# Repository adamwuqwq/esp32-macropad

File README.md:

# macropad

## Introduction
A low-budget macro numeric keypad based on ESP32 MCU and CH9329 USB HID emulation chip.  

## Functions
### Keys and Layout
1. Standard 10-key layout + 5 function keys
2. All key macro support
3. Up to 5 macro profiles (stored in MCU's internal storage)

### Connectivity
1. USB 2.0 HID (CH9329 based) 
2. Built-in USB hub, 1 external USB port, 1 internal USB (based on FE1.1s)
3. USB UART debugging (based on CH340C)
4. Bluetooth 4.2 BLE HID   
5. 2.4GHz Wi-Fi (for configuration and OTA firmware update)

### Power Supply & Power Management
1. 3.7V Li-ion battery charging and management (based on TP5400)
2. Supports MCU's deep sleep and hibernation. 

### UI & User Interaction
1. 0.91' built-in I2C OLED screen
2. Cross-platform configuration App on PC using Qt/PyQt
3. Web configuration interface

### Others
1. USB HID Mouse emulation
2. TBD

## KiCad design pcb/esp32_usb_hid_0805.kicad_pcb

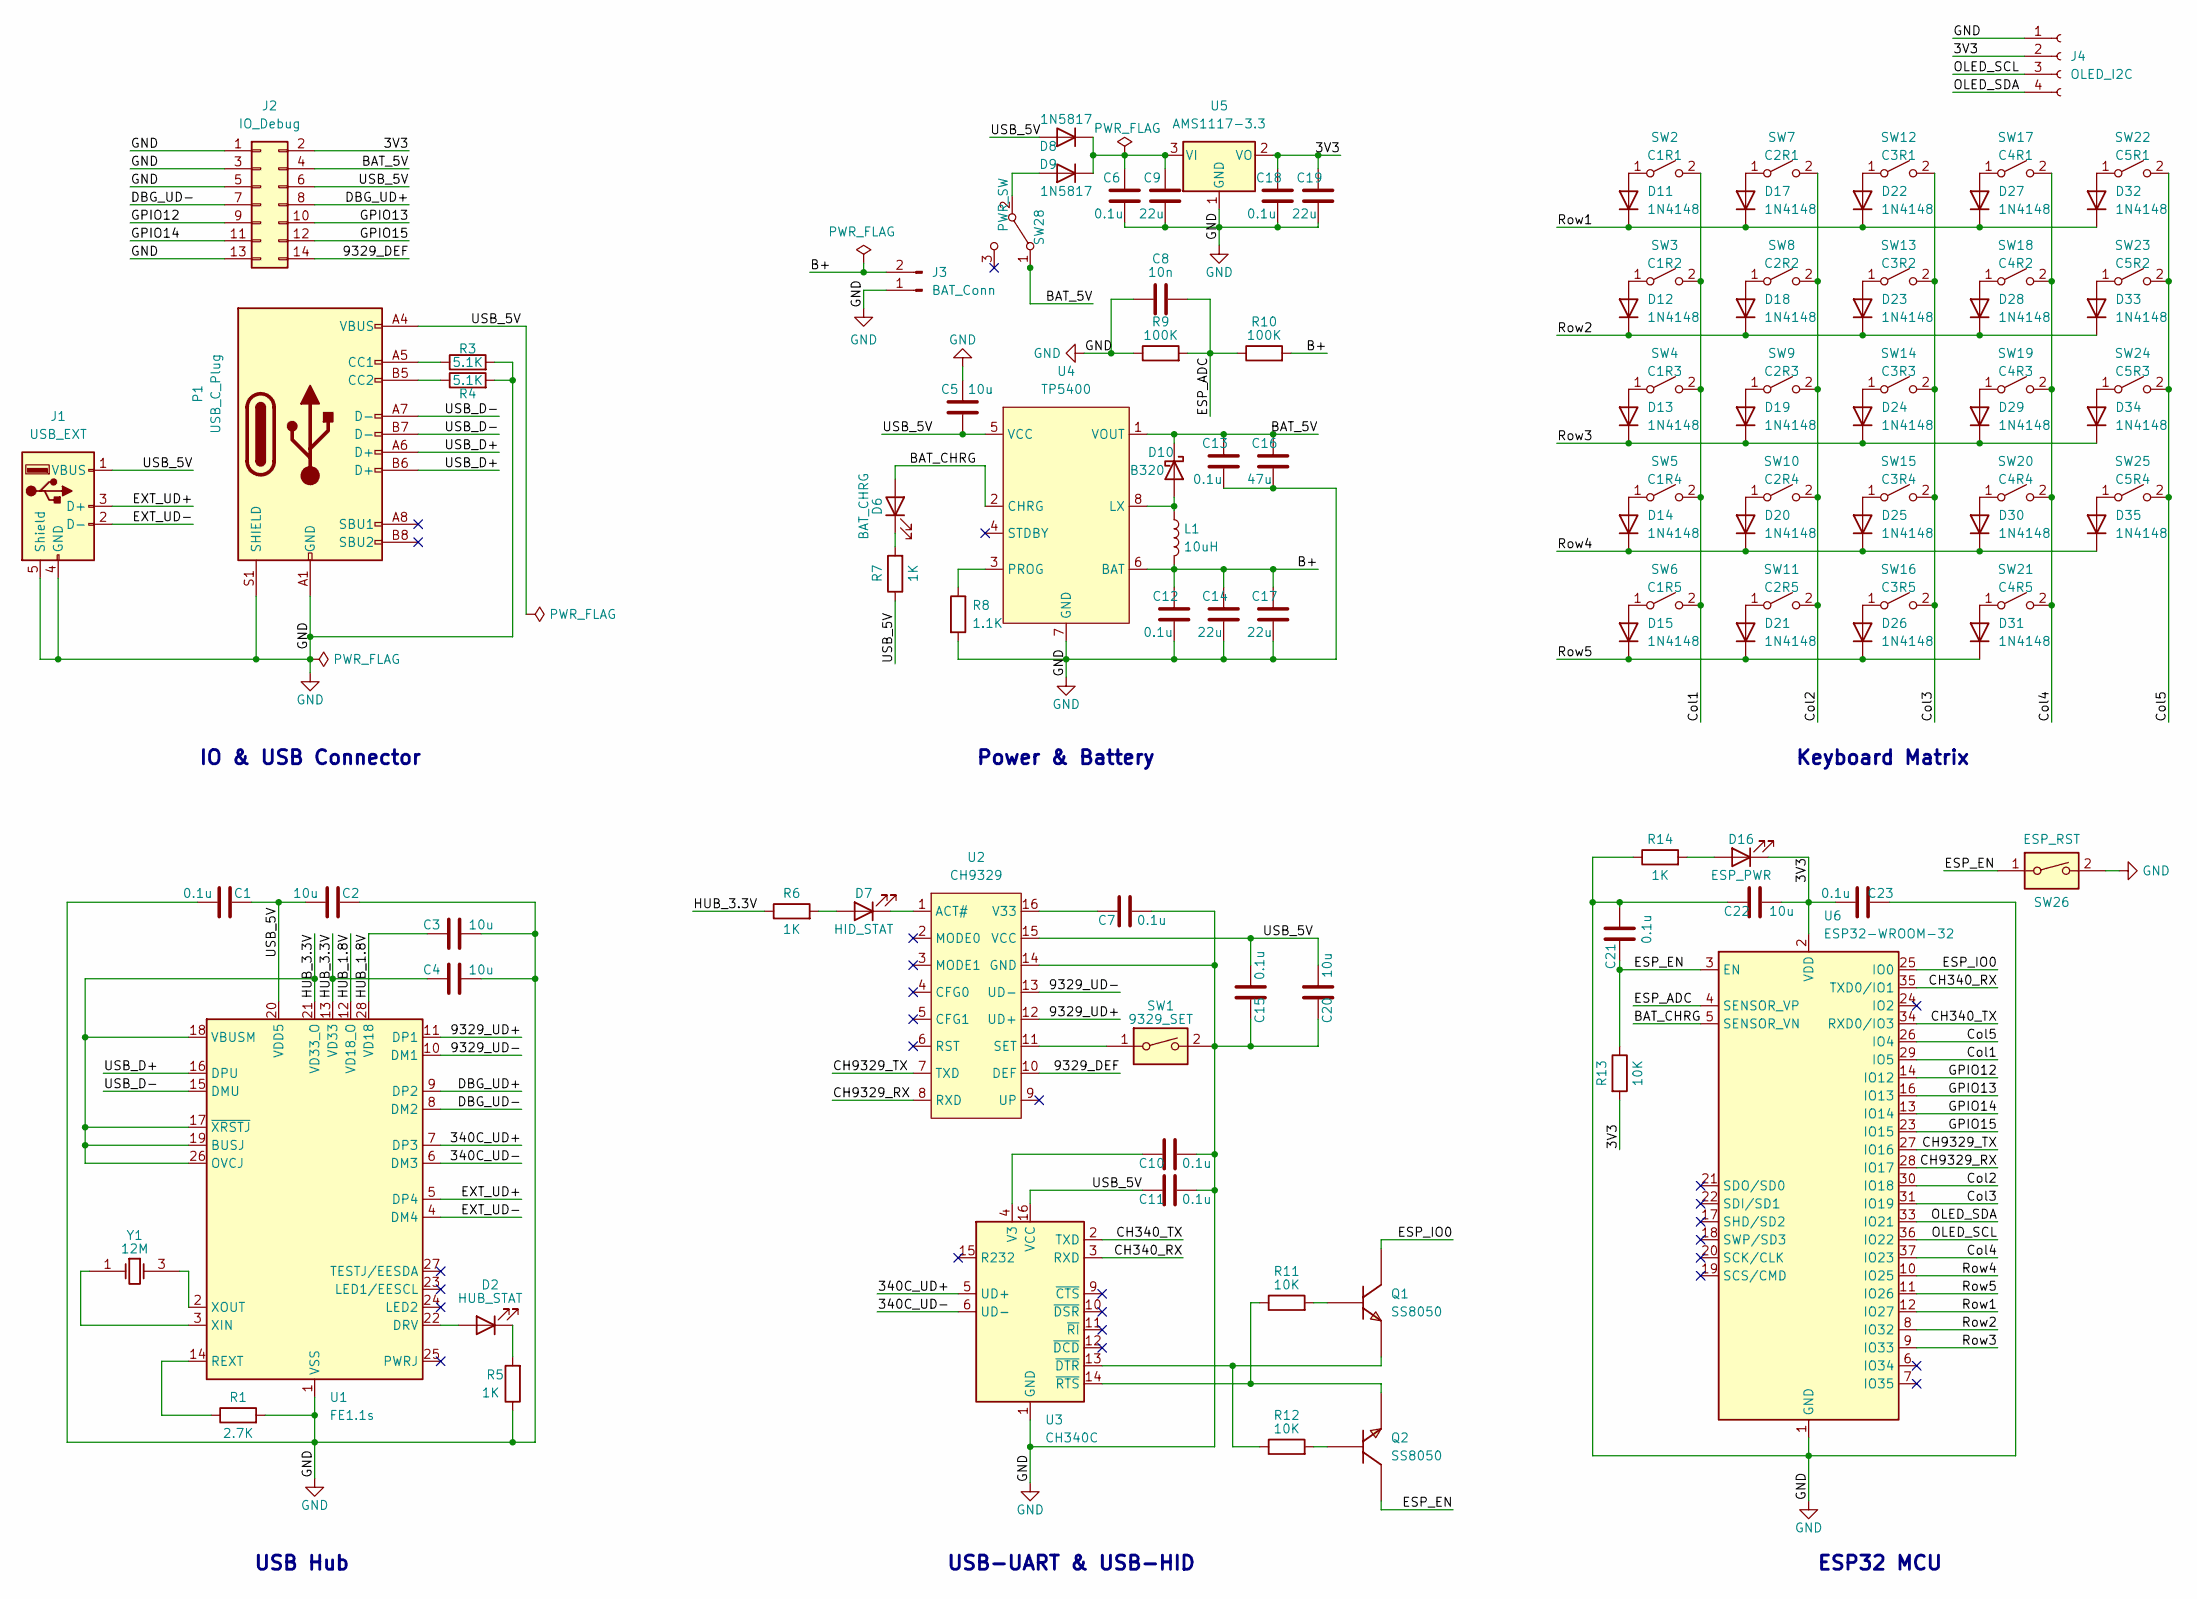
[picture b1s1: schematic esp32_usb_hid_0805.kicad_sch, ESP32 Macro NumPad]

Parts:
C1, C6, C7, C10, C11, C12, C13, C15, C18, C21, C23: 0.1u; C_0805_2012Metric
C2, C3, C4, C5, C20, C22: 10u; C_0805_2012Metric
C8: 10n; C_0805_2012Metric
C9, C14, C17, C19: 22u; C_0805_2012Metric
C16: 47u; C_0805_2012Metric
D2: HUB_STAT; LED_0805_2012Metric
D6: BAT_CHRG; LED_0805_2012Metric
D7: HID_STAT; LED_0805_2012Metric
D8, D9: 1N5817; D_SOD-123
D10: B320; D_SMA
D11, D12, D13, D14, D15, D17, D18, D19, D20, D21, D22, D23, D24, D25, D26, D27, D28, D29, D30, D31, D32, D33, D34, D35: 1N4148; D_SOD-123
D16: ESP_PWR; LED_0805_2012Metric
J1: USB_EXT; USB_A_Stewart_SS-52100-001_Horizontal
J2: IO_Debug; PinHeader_2x08_P2.54mm_Vertical
J3: BAT_Conn; PinHeader_2x01_P2.00mm_Vertical_SMD
J4: OLED_I2C; PinSocket_1x04_P2.54mm_Vertical
L1: 10uH; L_Coilcraft_XxL4020
P1: USB_C_Plug; USB_C_Receptacle_GCT_USB4085
Q1, Q2: SOT-23_SS8050_Y1; SOT-23
R1: 2.7K; R_0805_2012Metric
R3, R4: 5.1K; R_0805_2012Metric
R5, R6, R7, R14: 1K; R_0805_2012Metric
R8: 1.1K; R_0805_2012Metric
R9, R10: 100K; R_0805_2012Metric
R11, R12, R13: 10K; R_0805_2012Metric
SW1: 9329_SET; SW_SPST_CK_RS282G05A3
SW2: C1R1; SW_Cherry_MX_1.00u_PCB
SW3: C1R2; SW_Cherry_MX_1.00u_PCB
SW4: C1R3; SW_Cherry_MX_1.00u_PCB
SW5: C1R4; SW_Cherry_MX_1.00u_PCB
SW6: C1R5; SW_Cherry_MX_1.00u_PCB
SW7: C2R1; SW_Cherry_MX_1.00u_PCB
SW8: C2R2; SW_Cherry_MX_1.00u_PCB
SW9: C2R3; SW_Cherry_MX_1.00u_PCB
SW10: C2R4; SW_Cherry_MX_1.00u_PCB
SW11: C2R5; SW_Cherry_MX_1.00u_PCB
SW12: C3R1; SW_Cherry_MX_1.00u_PCB
SW13: C3R2; SW_Cherry_MX_1.00u_PCB
SW14: C3R3; SW_Cherry_MX_1.00u_PCB
SW15: C3R4; SW_Cherry_MX_1.00u_PCB
SW16: C3R5; SW_Cherry_MX_1.00u_PCB
SW17: C4R1; SW_Cherry_MX_1.00u_PCB
SW18: C4R2; SW_Cherry_MX_1.00u_PCB
SW19: C4R3; SW_Cherry_MX_1.00u_PCB
SW20: C4R4; SW_Cherry_MX_1.00u_PCB
SW21: C4R5; SW_Cherry_MX_1.00u_PCB
SW22: C5R1; SW_Cherry_MX_1.00u_PCB
SW23: C5R2; SW_Cherry_MX_1.00u_PCB
SW24: C5R3; SW_Cherry_MX_1.00u_PCB
SW25: C5R4; SW_Cherry_MX_2.00u_Vertical_PCB
SW26: ESP_RST; SW_SPST_CK_RS282G05A3
SW28: PWR_SW; SW_SPDT_PCM12
U1: FE1.1s; SSOP-28_3.9x9.9mm_P0.635mm
U2: CH9329; SOP-16_3.9x9.9mm_P1.27mm
U3: CH340C; SOIC-16_3.9x9.9mm_P1.27mm
U4: TP5400; HTSOP-8-1EP_3.9x4.9mm_P1.27mm_EP2.4x3.2mm
U5: AMS1117-3.3; SOT-223-3_TabPin2
U6: ESP32-WROOM-32
Y1: SMD-3225_4P__12MHZ_20PF_10PPM; Crystal_SMD_TXC_7M-4Pin_3.2x2.5mm

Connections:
/3V3: C18.1, C19.1, C22.2, C23.2, D16.1 (K), J2.2, J4.2, R13.2, U5.2 (VO), U6.2 (VDD)
/340C_UD+: U1.7 (DP3), U3.5 (UD+)
/340C_UD-: U1.6 (DM3), U3.6 (UD-)
/9329_DEF: J2.14, U2.10 (DEF)
/9329_UD+: U1.11 (DP1), U2.12 (UD+)
/9329_UD-: U1.10 (DM1), U2.13 (UD-)
/B+: C12.1, C14.1, C17.1, J3.2, L1.2, R10.2, U4.6 (BAT)
/BAT_5V: C13.1, C16.1, D10.1 (K), J2.4, SW28.1 (A), U4.1 (VOUT)
/BAT_CHRG: D6.2 (A), U4.2 (CHRG), U6.5 (SENSOR_VN)
/CH340_RX: U3.3 (RXD), U6.35 (TXD0/IO1)
/CH340_TX: U3.2 (TXD), U6.34 (RXD0/IO3)
/CH9329_RX: U2.8 (RXD), U6.28 (IO17)
/CH9329_TX: U2.7 (TXD), U6.27 (IO16)
/Col1: SW2.2 (B), SW3.2 (B), SW4.2 (B), SW5.2 (B), SW6.2 (B), U6.29 (IO5)
/Col2: SW7.2 (B), SW8.2 (B), SW9.2 (B), SW10.2 (B), SW11.2 (B), U6.30 (IO18)
/Col3: SW12.2 (B), SW13.2 (B), SW14.2 (B), SW15.2 (B), SW16.2 (B), U6.31 (IO19)
/Col4: SW17.2 (B), SW18.2 (B), SW19.2 (B), SW20.2 (B), SW21.2 (B), U6.37 (IO23)
/Col5: SW22.2 (B), SW23.2 (B), SW24.2 (B), SW25.2 (B), U6.26 (IO4)
/DBG_UD+: J2.8, U1.9 (DP2)
/DBG_UD-: J2.7, U1.8 (DM2)
/ESP_ADC: C8.2, R9.2, R10.1, U6.4 (SENSOR_VP)
/ESP_EN: C21.1, Q2.3 (C), R13.1, SW26.1, U6.3 (EN)
/ESP_IO0: Q1.3 (C), U6.25 (IO0)
/EXT_UD+: J1.3 (D+), U1.5 (DP4)
/EXT_UD-: J1.2 (D-), U1.4 (DM4)
/GPIO12: J2.9, U6.14 (IO12)
/GPIO13: J2.10, U6.16 (IO13)
/GPIO14: J2.11, U6.13 (IO14)
/GPIO15: J2.12, U6.23 (IO15)
/HUB_1.8V: C3.1, U1.12 (VD18_O), U1.28 (VD18)
/HUB_3.3V: C4.1, R6.1, U1.13 (VD33), U1.17 (~XRSTJ), U1.18 (VBUSM), U1.19 (BUSJ), U1.21 (VD33_O), U1.26 (OVCJ)
/OLED_SCL: J4.3, U6.36 (IO22)
/OLED_SDA: J4.4, U6.33 (IO21)
/Row1: D11.1 (K), D17.1 (K), D22.1 (K), D27.1 (K), D32.1 (K), U6.12 (IO27)
/Row2: D12.1 (K), D18.1 (K), D23.1 (K), D28.1 (K), D33.1 (K), U6.8 (IO32)
/Row3: D13.1 (K), D19.1 (K), D24.1 (K), D29.1 (K), D34.1 (K), U6.9 (IO33)
/Row4: D14.1 (K), D20.1 (K), D25.1 (K), D30.1 (K), D35.1 (K), U6.10 (IO25)
/Row5: D15.1 (K), D21.1 (K), D26.1 (K), D31.1 (K), U6.11 (IO26)
/USB_5V: C1.1, C2.2, C5.2, C11.2, C15.2, C20.2, D8.2 (A), J1.1 (VBUS), J2.6, P1.A4 (VBUS), P1.A9 (VBUS), P1.B4 (VBUS), P1.B9 (VBUS), R7.1, U1.20 (VDD5), U2.15 (VCC), U3.16 (VCC), U4.5 (VCC)
/USB_D+: P1.A6 (D+), P1.B6 (D+), U1.16 (DPU)
/USB_D-: P1.A7 (D-), P1.B7 (D-), U1.15 (DMU)
GND: C1.2, C2.1, C3.2, C4.2, C5.1, C6.2, C7.2, C8.1, C9.2, C10.2, C11.1, C12.2, C13.2, C14.2, C15.1, C16.2, C17.2, C18.2, C19.2, C20.1, C21.2, C22.1, C23.1, J1.4 (GND), J1.5 (Shield), J2.1, J2.3, J2.5, J2.13, J3.1, J4.1, P1.A1 (GND), P1.A12 (GND), P1.B1 (GND), P1.B12 (GND), P1.S1 (SHIELD), R1.2, R3.2, R4.2, R5.1, R8.2, R9.1, R14.1, SW1.2, SW26.2, U1.1 (VSS), U2.14 (GND), U3.1 (GND), U4.7 (GND), U5.1 (GND), U6.1 (GND), U6.15 (GND), U6.38 (GND), U6.39 (GND)
unnamed: C6.1, C9.1, D8.1 (K), D9.1 (K), U5.3 (VI)
unnamed: C7.1, U2.16 (V33)
unnamed: C10.1, U3.4 (V3)
unnamed: D2.1 (K), R5.2
unnamed: D2.2 (A), U1.22 (DRV)
unnamed: D7.1 (K), U2.1 (ACT#)
unnamed: D7.2 (A), R6.2
unnamed: D9.2 (A), SW28.2 (B)
unnamed: D10.2 (A), L1.1, U4.8 (LX)
unnamed: D11.2 (A), SW2.1 (A)
unnamed: D12.2 (A), SW3.1 (A)
unnamed: D13.2 (A), SW4.1 (A)
unnamed: D14.2 (A), SW5.1 (A)
unnamed: D15.2 (A), SW6.1 (A)
unnamed: D16.2 (A), R14.2
unnamed: D17.2 (A), SW7.1 (A)
unnamed: D18.2 (A), SW8.1 (A)
unnamed: D19.2 (A), SW9.1 (A)
unnamed: D20.2 (A), SW10.1 (A)
unnamed: D21.2 (A), SW11.1 (A)
unnamed: D22.2 (A), SW12.1 (A)
unnamed: D23.2 (A), SW13.1 (A)
unnamed: D24.2 (A), SW14.1 (A)
unnamed: D25.2 (A), SW15.1 (A)
unnamed: D26.2 (A), SW16.1 (A)
unnamed: D27.2 (A), SW17.1 (A)
unnamed: D28.2 (A), SW18.1 (A)
unnamed: D29.2 (A), SW19.1 (A)
unnamed: D30.2 (A), SW20.1 (A)
unnamed: D31.2 (A), SW21.1 (A)
unnamed: D32.2 (A), SW22.1 (A)
unnamed: D33.2 (A), SW23.1 (A)
unnamed: D34.2 (A), SW24.1 (A)
unnamed: D35.2 (A), SW25.1 (A)
unnamed: P1.A5 (CC1), R3.1
unnamed: P1.B5 (CC2), R4.1
unnamed: Q1.1 (B), R11.2
unnamed: Q1.2 (E), R12.1, U3.13 (~DTR)
unnamed: Q2.1 (B), R12.2
unnamed: Q2.2 (E), R11.1, U3.14 (~RTS)
unnamed: R1.1, U1.14 (REXT)
unnamed: D6.1 (K), R7.2
unnamed: R8.1, U4.3 (PROG)
unnamed: SW1.1, U2.11 (SET)
unnamed: U1.2 (XOUT), Y1.3 (OSC2)
unnamed: U1.3 (XIN), Y1.1 (OSC1)

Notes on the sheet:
USB Hub
Keyboard Matrix
USB-UART & USB-HID
Power & Battery
IO & USB Connector
ESP32 MCU

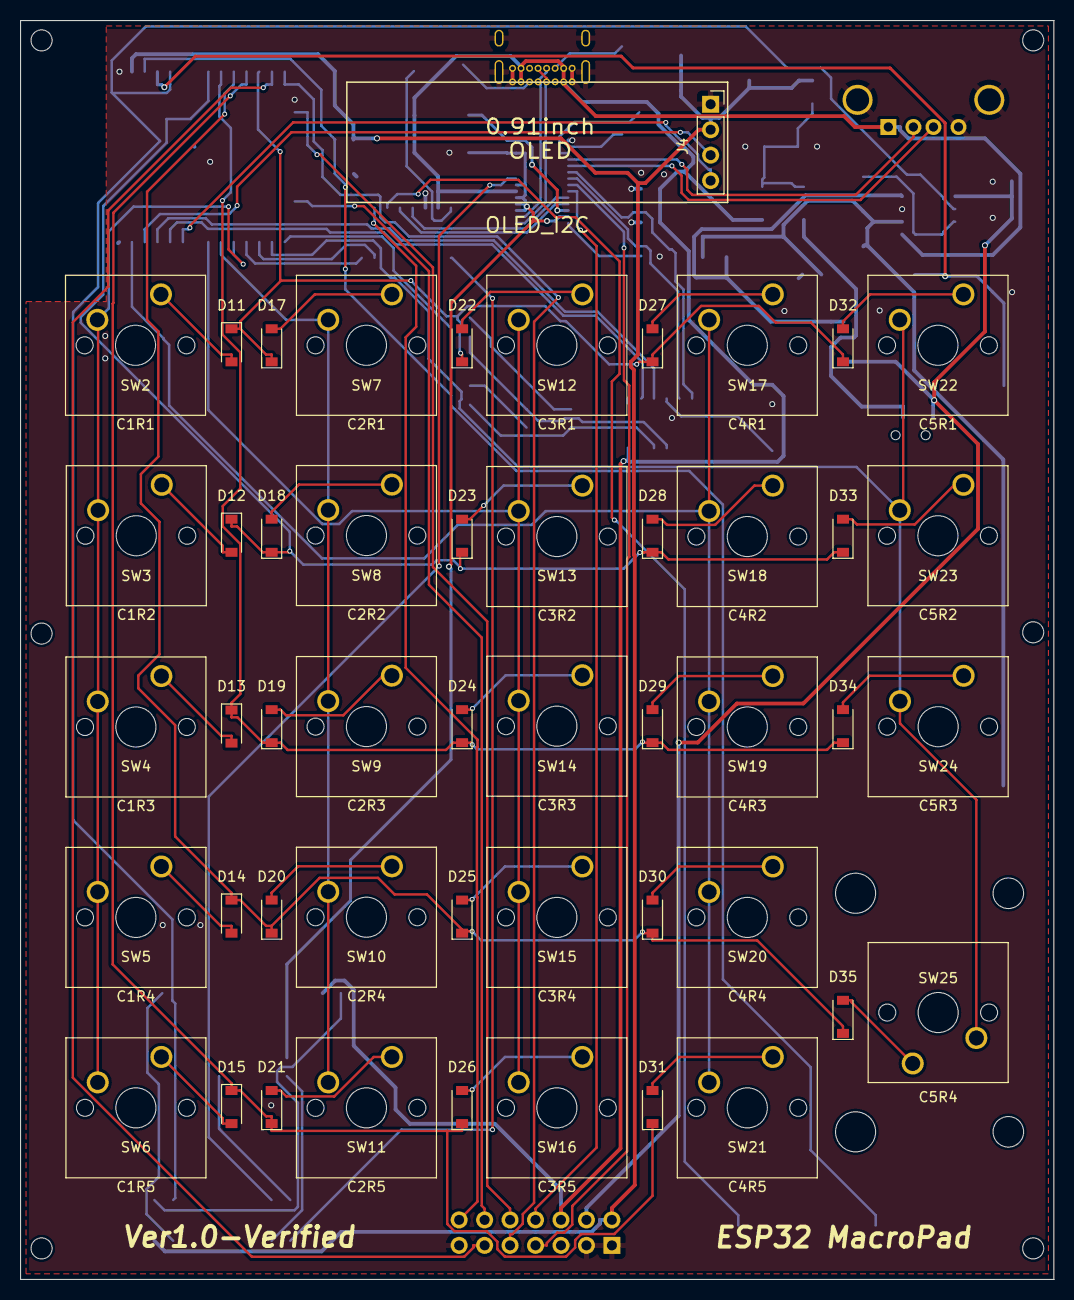
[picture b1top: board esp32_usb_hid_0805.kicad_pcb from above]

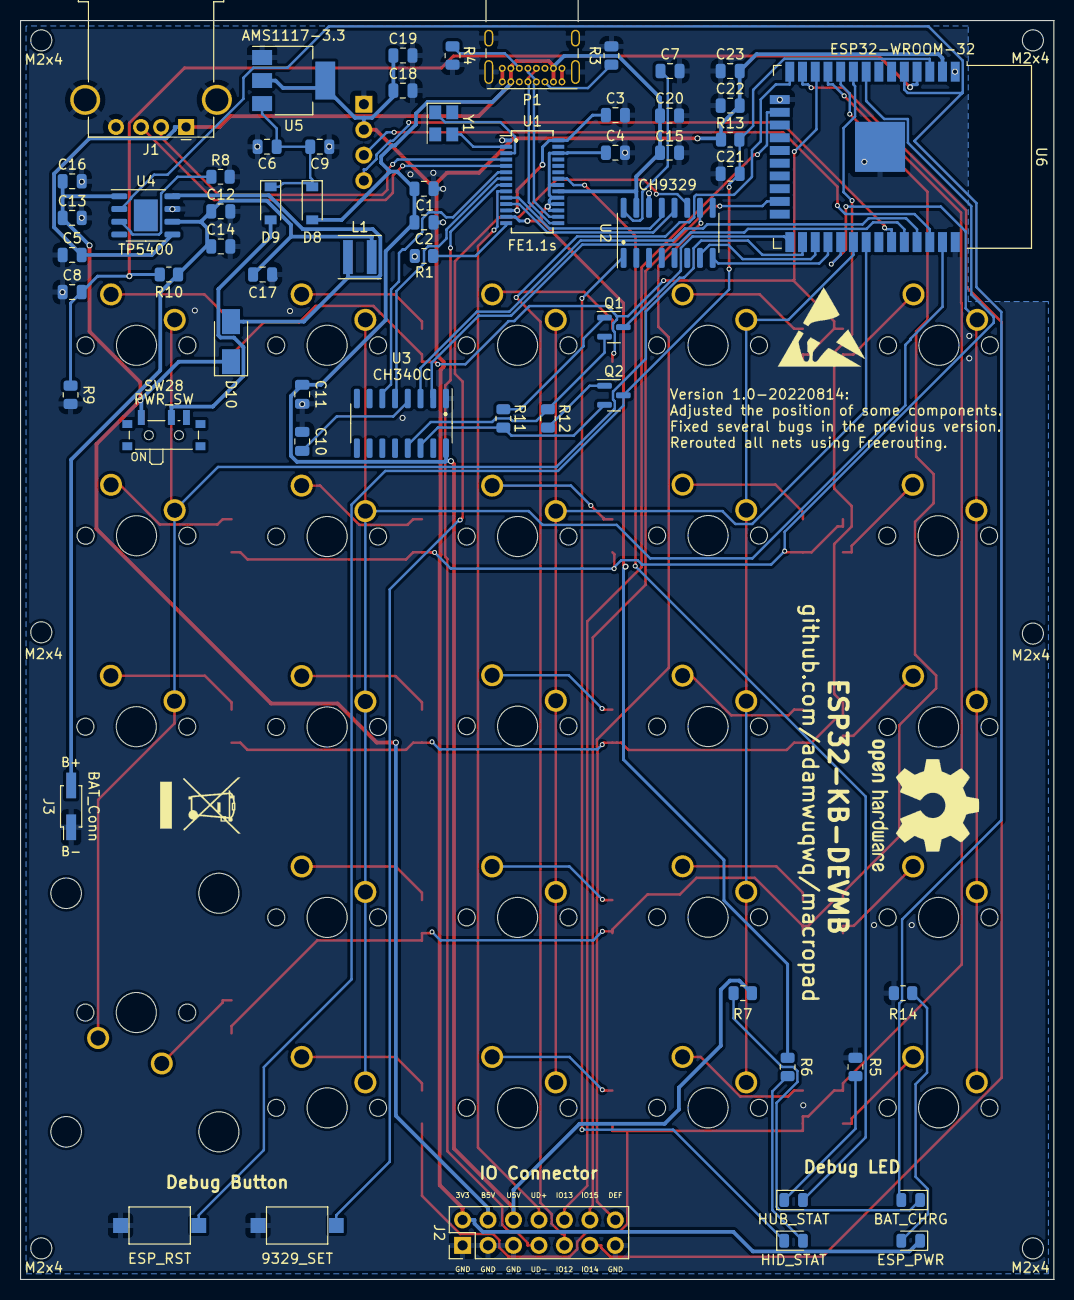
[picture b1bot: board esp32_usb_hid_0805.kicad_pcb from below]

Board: 2 copper layers, 103.1 x 125.6 mm, 109 parts (60 on the bottom side), 88 nets.

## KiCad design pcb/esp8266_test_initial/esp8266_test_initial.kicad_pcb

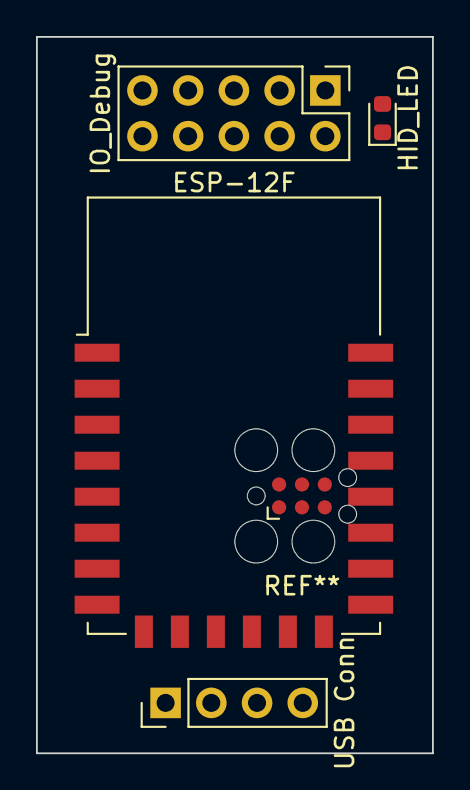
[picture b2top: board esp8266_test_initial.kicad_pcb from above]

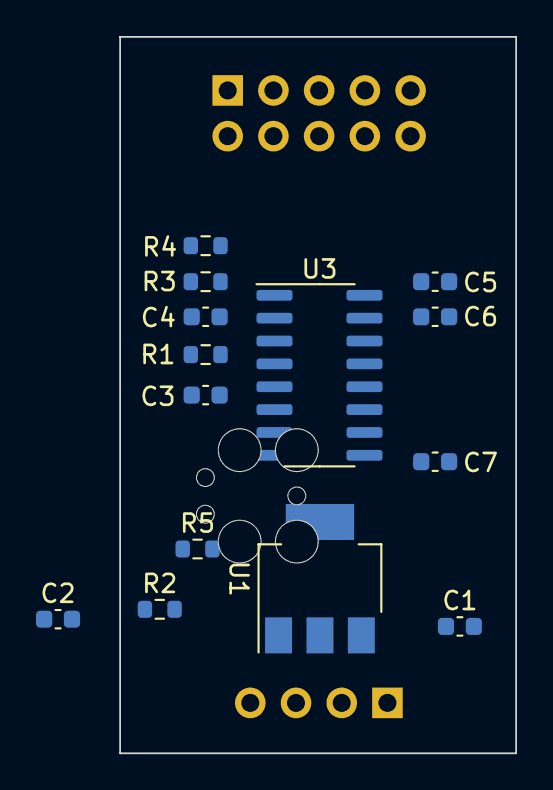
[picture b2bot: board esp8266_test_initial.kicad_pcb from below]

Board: 2 copper layers, 22.0 x 39.8 mm, 18 parts (14 on the bottom side), 19 nets, no tracks yet.

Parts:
C1, C3: 22uF; C_0603_1608Metric
C2, C4, C5, C6: 0.1uF; C_0603_1608Metric
C7: 10uF; C_0603_1608Metric
D1: HID_LED; LED_0603_1608Metric
J1: USB Conn; PinHeader_1x04_P2.54mm_Vertical
J2: IO_Debug; PinHeader_2x05_P2.54mm_Vertical
R1, R2, R4, R5: 10k; R_0603_1608Metric
R3: 3.3k; R_0603_1608Metric
U1: AMS1117-3.3; SOT-223-3_TabPin2
U2: ESP-12F; ESP-12E
U3: CH9329; SOP-16_3.9x9.9mm_P1.27mm

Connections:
+5V: C1.2, C2.2, C6.1, C7.1, J1.1, U1.3 (VI), U3.15 (VCC)
/ESP_DL: J2.3, R4.2, U2.18 (GPIO0)
/ESP_RXD: J2.7, U2.21 (GPIO3/RXD)
/ESP_TXD: J2.5, U2.22 (GPIO1/TXD)
/GPIO12: J2.9, U2.6 (GPIO12)
/GPIO13: J2.6, U2.7 (GPIO13)
/GPIO14: J2.8, U2.5 (GPIO14)
/GPIO15: J2.10, R5.1, U2.16 (GPIO15)
/HID_DL: J2.1, U3.11 (SET)
GND: C1.1, C2.1, C3.1, C4.1, C5.1, C6.2, C7.2, J1.4, J2.2, J2.4, R5.2, U1.1 (GND), U2.15 (GND), U3.14 (GND)
unnamed: C3.2, C4.2, R1.1, R2.1, R3.1, R4.1, U1.2 (VO), U2.8 (VCC)
unnamed: C5.2, U3.16 (V33)
unnamed: D1.1 (K), U3.1 (ACT#)
unnamed: D1.2 (A), R3.2
unnamed: J1.2, U3.12 (UD+)
unnamed: J1.3, U3.13 (UD-)
unnamed: R1.2, U2.3 (EN)
unnamed: R2.2, U2.1 (~RST)
unnamed: U2.17 (GPIO2), U3.8 (RXD)

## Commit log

2022-03-19 Added document file for zh-cn and edited .gitignore
2022-03-20 Created KiCAD project files, added documents and tools for CH9329
2022-03-27 Added datasheet files for ESP-12F module
2022-03-28 Updated ESP8266_test_initial's kiCAD PCB file
2022-04-06 Added datasheet for esp32,fe1.1s,tp5400,ch340c,ams1117
2022-04-06 Updated KiCAD Schematic and PCB file, version 0.4-alpha
2022-04-06 Updated readme file: ESP8266 -> ESP32
2023-07-12 Update HW document
2023-07-12 Sample for SSD1306 OLED
2023-07-12 Update PCB design
